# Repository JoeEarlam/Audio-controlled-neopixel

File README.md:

# Audio-controlled-neopixel

Filters an incoming line level audio signal into three bandpassed frequency "bins", which output to a peak detect sample and hold circuit. These sample and holds are sampled by the Arduino ADC, and the three frequencies (bass, mid, treble) become RGB on a Neopixel compatible LED strip.

There are a few different patterns currently written - a mixture of sound activated, random, block updated and "chasing lights" patterns.

# Hardware Notes, in no particular order.

There are two options for power. +5V only using a Tracopower TMA0512D to generate the +/-12V voltages required for the analogue components, or external +/-12V and 5V. 5V only is preferred for simplicity, but the TMA0512D isn't a typical parts bin find (and is the single most expensive component on the board), so an external power header has been added for operation without.

The level potentiometer allows a wide range of signals to be used. Turn it up until the peak light begins to flash, then down a little. This gives you maximum brightness from the Neopixel strip without clipping.

Follow Adafruit's guidance on Neopixel power supplies - the 5V rail will need to be beefy. The PCB can handle up to around 5A - ensure the fitted fuse is suitable.

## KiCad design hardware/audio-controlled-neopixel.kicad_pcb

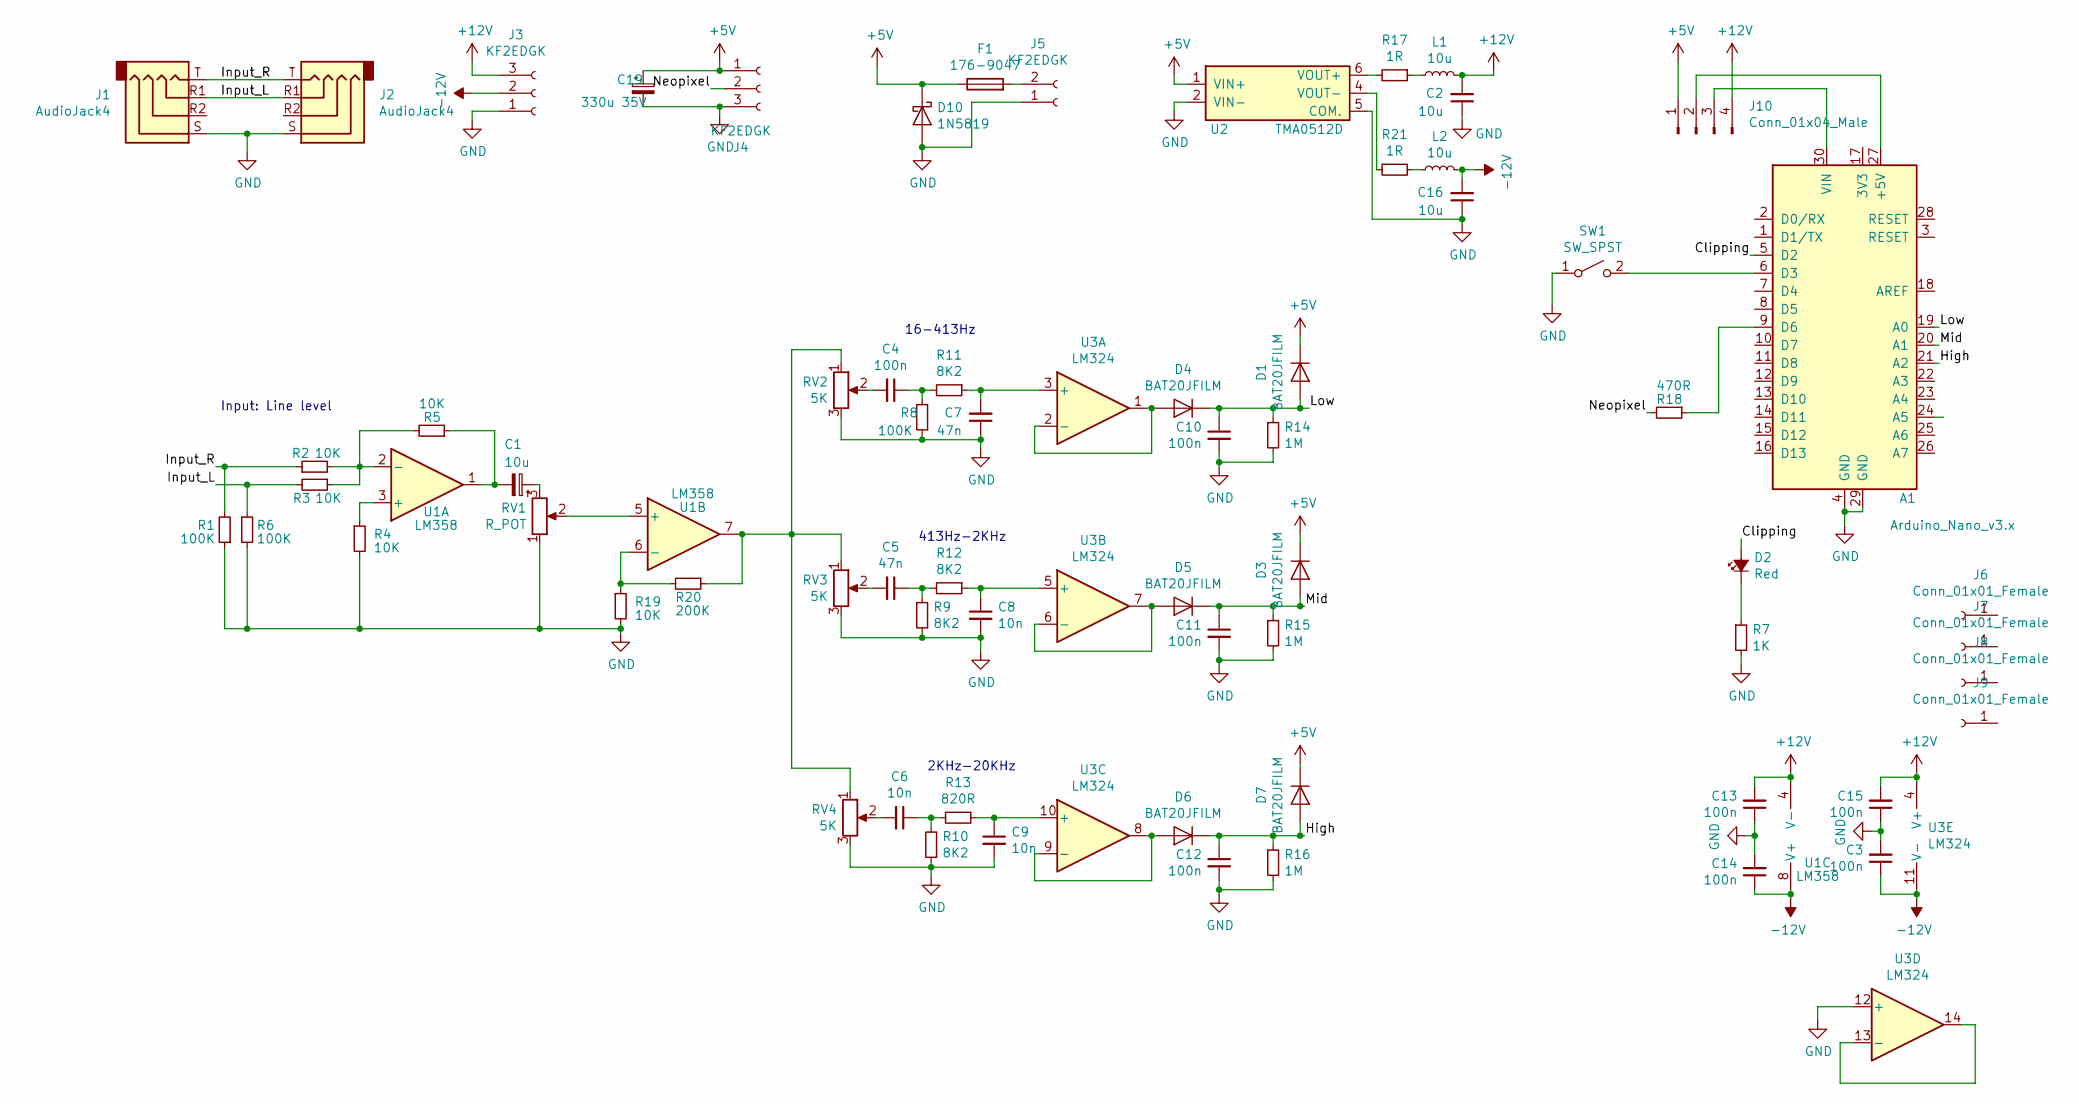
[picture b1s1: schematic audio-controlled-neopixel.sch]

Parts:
A1: Arduino_Nano_v3.x; Arduino_Nano
C1: 10u; CP_Radial_D5.0mm_P2.00mm
C2, C16: 10u; C_0805_2012Metric
C3, C4, C10, C11, C12, C13, C14, C15: 100n; C_0805_2012Metric
C5, C7: 47n; C_0805_2012Metric
C6, C8, C9: 10n; C_0805_2012Metric
C19: 330u 35V; CP_Elec_10x10
D1, D3, D4, D5, D6, D7: BAT20JFILM; D_SOD-323
D2: Red; LED_0805_2012Metric
D10: 1N5819; D_SOD-123
F1: 176-9047; 5x20_holder
J1, J2: AudioJack4; Jack_3.5mm_PJ320D_Horizontal
J3: KF2EDGK; TerminalBlock_Phoenix_MPT-0,5-3-2.54_1x03_P2.54mm_Horizontal
J4: KF2EDGK; PhoenixContact_MSTBA_2,5_3-G-5,08_1x03_P5.08mm_Horizontal
J5: KF2EDGK; PhoenixContact_MSTBA_2,5_2-G_1x02_P5.00mm_Horizontal
J6, J7, J8, J9: Conn_01x01_Female; MountingHole_3.2mm_M3
J10: Conn_01x04_Male; PinHeader_1x04_P2.54mm_Vertical
L1, L2: 10u; L_0805_2012Metric
R1, R6, R8: 100K; R_0805_2012Metric
R2, R3, R4, R5, R19: 10K; R_0805_2012Metric
R7: 1K; R_0805_2012Metric
R9, R10, R11, R12: 8K2; R_0805_2012Metric
R13: 820R; R_0805_2012Metric
R14, R15, R16: 1M; R_0805_2012Metric
R17, R21: 1R; R_0805_2012Metric
R18: 470R; R_0805_2012Metric
R20: 200K; R_0805_2012Metric
RV1: R_POT; Potentiometer_Alps_RK097_Single_Horizontal
RV2, RV3, RV4: 5K; Potentiometer_Vishay_TS53YJ_Vertical; Part Number EVM3YSX50B53
SW1: SW_SPST; SW_Tactile_SKHH_Angled
U1: LM358; SOIC-8_3.9x4.9mm_P1.27mm
U2: TMA0512D; TMAxxxxD; Manufacturer_Part_Number TMA 2412D; Mouser Part Number 495-TMA-2412D
U3: LM324; SOIC-14_3.9x8.7mm_P1.27mm

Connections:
+5V: C19.1, D1.1 (K), D3.1 (K), D7.1 (K), D10.1 (K), F1.1, J4.1, J10.1, U2.1 (VIN+)
+12V: C2.2, C13.2, C15.2, J3.3, J10.4, L1.2, U1.4 (V-), U3.4 (V+)
-12V: C3.1, C14.1, C16.2, J3.2, L2.2, U1.8 (V+), U3.11 (V-)
/Clipping: A1.5 (D2), D2.2 (A)
/High: A1.21 (A2), C12.1, D6.1 (K), D7.2 (A), R16.1
/Input_L: J1.R1, J2.R1, R3.2, R6.1
/Input_R: J1.T, J2.T, R1.2, R2.1
/Low: A1.19 (A0), C10.1, D1.2 (A), D4.1 (K), R14.1
/Mid: A1.20 (A1), C11.1, D3.2 (A), D5.1 (K), R15.1
/Neopixel: J4.2, R18.2
GND: A1.4 (GND), A1.29 (GND), C2.1, C3.2, C7.1, C8.2, C9.2, C10.2, C11.2, C12.2, C13.1, C14.2, C15.1, C16.1, C19.2, D10.2 (A), J1.S, J2.S, J3.1, J4.3, J5.1, R1.1, R4.2, R6.2, R7.2, R8.1, R9.1, R10.1, R14.2, R15.2, R16.2, R19.2, RV1.1, RV2.3, RV3.3, RV4.3, SW1.1 (A), U2.2 (VIN-), U2.5 (COM.), U3.12 (+)
unnamed: A1.6 (D3), SW1.2 (B)
unnamed: A1.9 (D6), R18.1
unnamed: A1.27 (+5V), J10.2
unnamed: A1.30 (VIN), J10.3
unnamed: C1.1, RV1.3
unnamed: C1.2, R5.1, U1.1
unnamed: C4.1, R8.2, R11.2
unnamed: C4.2, RV2.2
unnamed: C5.1, R9.2, R12.2
unnamed: C5.2, RV3.2
unnamed: C6.1, R10.2, R13.2
unnamed: C6.2, RV4.2
unnamed: C7.2, R11.1, U3.3 (+)
unnamed: C8.1, R12.1, U3.5 (+)
unnamed: C9.1, R13.1, U3.10 (+)
unnamed: D2.1 (K), R7.1
unnamed: D4.2 (A), U3.1, U3.2 (-)
unnamed: D5.2 (A), U3.6 (-), U3.7
unnamed: D6.2 (A), U3.8, U3.9 (-)
unnamed: F1.2, J5.2
unnamed: L1.1, R17.1
unnamed: L2.1, R21.1
unnamed: R2.2, R3.1, R5.2, U1.2 (-)
unnamed: R4.1, U1.3 (+)
unnamed: R17.2, U2.6 (VOUT+)
unnamed: R19.1, R20.2, U1.6 (-)
unnamed: R20.1, RV2.1, RV3.1, RV4.1, U1.7
unnamed: R21.2, U2.4 (VOUT-)
unnamed: RV1.2, U1.5 (+)
unnamed: U3.13 (-), U3.14

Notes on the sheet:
16-413Hz
413Hz-2KHz
2KHz-20KHz
Input: Line level

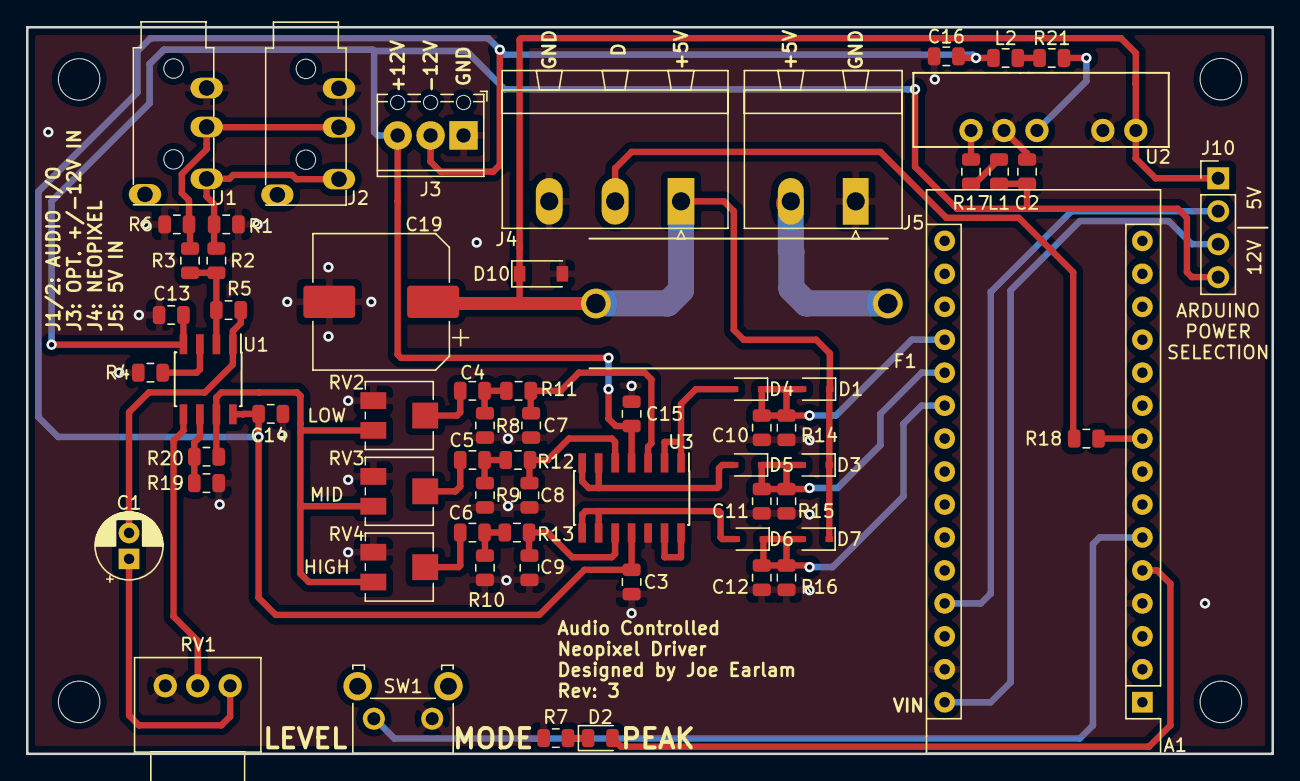
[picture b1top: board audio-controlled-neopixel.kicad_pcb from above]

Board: 2 copper layers, 96.0 x 56.0 mm, 68 parts (0 on the bottom side), 41 nets.

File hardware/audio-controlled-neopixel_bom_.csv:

Component,Description,Part,References,Value,Footprint,Quantity Per PCB,Datasheet
1,Arduino Nano v3.x,Arduino_Nano_v3.x,A1,Arduino_Nano_v3.x,Arduino_Nano,1,http://www.mouser.com/pdfdocs/Gravitech_Arduino_Nano3_0.pdf
2,Unpolarized capacitor,C_Small,C3 C4 C10 C11 C12 C13 C14 C15 C16 C20,100n,C_0805_2012Metric,10,~
3,Unpolarized capacitor,C_Small,C6 C8 C9,10n,C_0805_2012Metric,3,~
4,Polarised capacitor,CP_Small,C1 C2,10u,CP_Radial_D5.0mm_P2.00mm,2,~
5,Polarised capacitor,CP_Small,C19,330u 35V,CP_Radial_D10.0mm_P5.00mm,1,~
6,Unpolarized capacitor,C_Small,C5 C7,47n,C_0805_2012Metric,2,~
7,"100V 0.15A standard switching diode, DO-35",1N4148,D1 D4 D5 D6,1N4148,D_SOD-123,4,http://www.nxp.com/documents/data_sheet/1N4148_1N4448.pdf
8,"30V 0.2A Schottky barrier single diode, DO-35",BAT85,D3 D7 D8 D9 D10,1N5819,D_SOD-123,5,http://www.nxp.com/documents/data_sheet/BAT85.pdf
9,"LED, small symbol, alternativ symbol",LED_Small_ALT,D2,Red,LED_0805_2012Metric,1,~
10,"Fuse, generic",Fuse,F1,176-9047,5x20_holder,1,~
11,"Generic connector, single row, 01x03, script generated (kicad-library-utils/schlib/autogen/connector/)",Conn_01x03_Female,J2,KF2EDGK,"TerminalBlock_Phoenix_MPT-0,5-3-2.54_1x03_P2.54mm_Horizontal",1,~
12,"Generic connector, single row, 01x03, script generated (kicad-library-utils/schlib/autogen/connector/)",Conn_01x03_Female,J3,KF2EDGK,"PhoenixContact_MSTBA_2,5_3-G-5,08_1x03_P5.08mm_Horizontal",1,~
13,"Generic connector, single row, 01x02, script generated (kicad-library-utils/schlib/autogen/connector/)",Conn_01x02_Female,J4,KF2EDGK,"PhoenixContact_MSTBA_2,5_2-G_1x02_P5.00mm_Horizontal",1,~
14,"Generic connector, single row, 01x06, script generated (kicad-library-utils/schlib/autogen/connector/)",Conn_01x06_Female,J1,Phoenix MPT,"TerminalBlock_Phoenix_MPT-0,5-6-2.54_1x06_P2.54mm_Horizontal",1,~
15,"Resistor, small symbol",R_Small,R1 R8,100K,R_0805_2012Metric,2,~
16,"Resistor, small symbol",R_Small,R2 R3 R4 R17,10K,R_0805_2012Metric,4,~
17,"Resistor, small symbol",R_Small,R7,1K,R_0805_2012Metric,1,~
18,"Resistor, small symbol",R_Small,R6 R14 R15 R16,1M,R_0805_2012Metric,4,~
19,"Resistor, small symbol",R_Small,R5,200K,R_0805_2012Metric,1,~
20,"Resistor, small symbol",R_Small,R18,470R,R_0805_2012Metric,1,~
21,"Resistor, small symbol",R_Small,R10 R12,7K5,R_0805_2012Metric,2,~
22,"Resistor, small symbol",R_Small,R13,820R,R_0805_2012Metric,1,~
23,"Resistor, small symbol",R_Small,R9 R11,8K2,R_0805_2012Metric,2,~
24,"Dual Potentiometer, separate units",R_POT_Dual_Separate,RV1,10KA,Potentiometer_Alps_RK097_Dual_Horizontal,1,
25,Single Pole Single Throw (SPST) switch,SW_SPST,SW1,SW_SPST,SW_Tactile_SKHH_Angled,1,
26,"Low-Power, Quad-Operational Amplifiers, DIP-14/SOIC-14/SSOP-14",LM324,U1 U3,LM324,SOIC-14_3.9x8.7mm_P1.27mm,2,http://www.ti.com/lit/ds/symlink/lm2902-n.pdf
27,Isolated DC/DC Converter,TMAxxxxD,U4,TMA0512D,TMAxxxxD,1,www.tracopower.com/products/ten20win.pdf
,,,,,,,
,,,,,,,
,,,,,,,
,,,,,,,
,,,,,,,
Component Groups:,27,,,,,,
Component Count:,57,,,,,,
Fitted Components:,57,,,,,,
Number of PCBs:,1,,,,,,
Total components:,57,,,,,,
Schematic Version:,,,,,,,
Schematic Date:,,,,,,,
BoM Date:,11/01/2019 11:36,,,,,,
Schematic Source:,C:\Users\jearlam\Documents\github\Audio-controlled-neopixel\hardware\audio-controlled-neopixel.sch,,,,,,
KiCad Version:,Eeschema (5.0.0),,,,,,

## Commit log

2018-11-14 Added software
2018-11-14 Tweaked filter values for treble in schematic, added gamma correction for LEDs.
2018-11-15 Updated schematic and PCB to use SMD components for ease of manufacture.
2018-11-15 Fixed minor PCB trace issues
2018-11-15 Added pdf schematic
2019-01-14 updated schematic to reduce component count, PCB update to match
2019-01-14 minor PCB clean up
2019-01-14 updated code with mode selection
2019-01-15 update schematic to use 3.5mm audio I/O
2019-01-15 clean up schematic and PCB
2019-01-15 add attenuator for peak level calibration
2019-01-21 added software modes
2019-01-23 added extra software modes
2019-01-23 updated some footprints and symbols
2019-01-23 PCB bugfix, rearranged code
2019-01-24 updated gitignore
2019-01-27 added frequency response graph
2019-01-27 added attenuators to keep frequency response flat
2019-01-28 Hacky fix for less sensitive blue channel
2019-01-29 Updated frequency response graph
2019-01-30 fixed library issue with schematic
2019-02-04 added attenuators to balance frequency response
2019-02-05 removed analogue clipping hardware to prepare for transisiton to software solution (not implemented)
2019-02-07 tag for prototype production
2019-02-07 minor silkscreen changes
2019-02-13 added input resistors
2019-02-19 Cleaned up schematic, refactored code for latest hardware
2019-02-28 connect both op-amps to dual supply
2019-03-05 adjusted component values for better real world performance, changed diode types, minor PCB changes for better ground return paths
2019-03-10 updated software so clipping LED actually works
2019-07-16 hardware updates
2019-07-16 added power supply filtering
2019-07-26 as sent to production 26/07/19
